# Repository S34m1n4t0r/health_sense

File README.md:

# Health Sense

Health Sense is a repository that houses the design files for a portable sensor module specifically designed to measure the light intensity in the spectrum of the human eye. This module is primarily developed for research purposes to accurately quantify the light exposure experienced by the human eye.

## Table of Contents
- [Introduction](#introduction)
- [Features](#features)
- [Revisions](#Revisions)
- [Sensors Used](#sensors-used)
- [Getting Started](#getting-started)
- [Usage](#usage)
- [Contributing](#contributing)
- [License](#license)

## Introduction

The human eye is highly sensitive to light, and prolonged exposure to certain intensities and spectrums can have various effects on our overall health and well-being. The Health Sense project aims to provide researchers with a reliable and portable tool for measuring light exposure and analyzing its impact on human subjects.

This repository contains the design files and relevant documentation for the Health Sense sensor module. By using this module, researchers can gather accurate data on light exposure, which can be further utilized for scientific studies, understanding circadian rhythms, evaluating the effects of light on sleep patterns, and other related research areas.

## Features

- **Portable Design**: The Health Sense sensor module is designed to be compact and portable, allowing researchers to easily carry and use it in different environments.
- **Light Intensity Measurement**: The module accurately measures the light intensity in the spectrum of the human eye, providing valuable data for research purposes.
- **Customizable Spectral Range**: Researchers can adjust the spectral range of measurement based on their specific requirements, enabling flexibility in studying different light sources.
- **Data Logging**: The module is equipped with data logging capabilities, allowing researchers to record and analyze light exposure data over extended periods of time.
- **User-Friendly Interface**: The sensor module includes a user-friendly interface, making it easy to operate and configure the device for different research settings.

## Revisions
### Prototyping
Breadboard setup created to verify the correct functionallity of all included sensors.

### Revision 1.0
Two prototypes are manufactured and assembled by hand as a final POC. The uC is loaded with the arduino-bootloader.

### Revision 1.1
Five prototypes are manufactured and assembled. Enclosure holes are milled with CNC.

### Known Issues
* Enable transistor for SIM800L not working
* SIM800L as solder-on pcb not optimal. 2/5 modules hat to be replaced.
* Charging current of 100mA could be increased
* Temperature Sensor of lipo not connected to charger IC

## Sensors Used

The Health Sense sensor module incorporates the following sensors:

- Ambient Light Sensor (BH1750): Measures light intensity in the visible spectrum.
- UV-B Sensor (GUVA-S12SD): Measures light intensity in the ultraviolet spectrum.
- Gyroscope Sensor (MPU-6050): Detects and measures orientation and rotation.
- RTC Clock (PCF8563TS): Provides accurate timekeeping functionality for scheduling and data timestamping.
- UMTS Module (SIM800L): Enables communication and data transmission via UMTS cellular network.

The integration of these sensors allows for comprehensive data collection and analysis related to light exposure in the context of research.

## Getting Started

To get started with the Health Sense sensor module, follow the steps below:

1. **Hardware Requirements**: Ensure you have the necessary components to assemble the sensor module. Refer to the [BOM](docs/BillOfMaterials_v1.1.csv) and [Schematic](HealthSenseSchematic_v1.1.pdf) for detailed information.

2. **Software Setup**: Install the Arduino IDE, the firmware hexfile can be generated using the arduino ide, choose the Nano Board. Flash the firmware via ISP connector J1.

3. **Calibration**: Before using the sensor module, it is important to calibrate it for accurate light intensity measurements.

4. **Usage**: Once the sensor module is assembled, calibrated, and ready, you can start using it to measure light exposure in your research. See the [Usage](#usage) section for more details.

## Usage

To utilize the Health Sense sensor module for measuring light exposure, follow these steps:

1. Connect the sensor module to a power source and ensure it is properly configured.

2. Position the module in the desired location to measure the light exposure of the human eye.

3. Initiate the measurement process by using the provided software interface or API. The module will start recording light intensity data in the specified spectral range.

4. Allow the module to collect data for the desired duration. The logged data can be stored internally or transmitted to an external device for analysis.

5. Analyze the collected data using appropriate data analysis tools to draw insights and conclusions regarding light exposure in your research.

Refer to the [User Guide](docs/user_guide.md) for detailed instructions on using the Health Sense sensor module effectively.

## Contributing

We welcome contributions from the community to enhance the Health Sense project. 

## License

The Health Sense project is licensed under the [GNU GENERAL PUBLIC LICENSE
](LICENSE). 

## Contact

For any inquiries or feedback regarding the Health Sense project, please contact our team. We appreciate your interest and support!

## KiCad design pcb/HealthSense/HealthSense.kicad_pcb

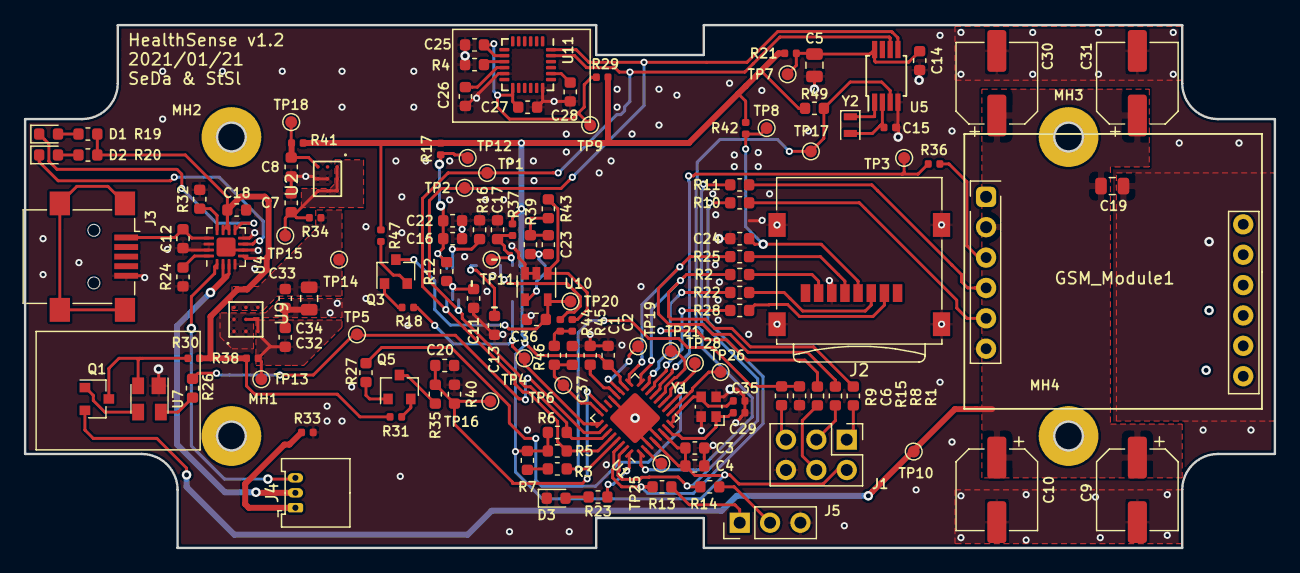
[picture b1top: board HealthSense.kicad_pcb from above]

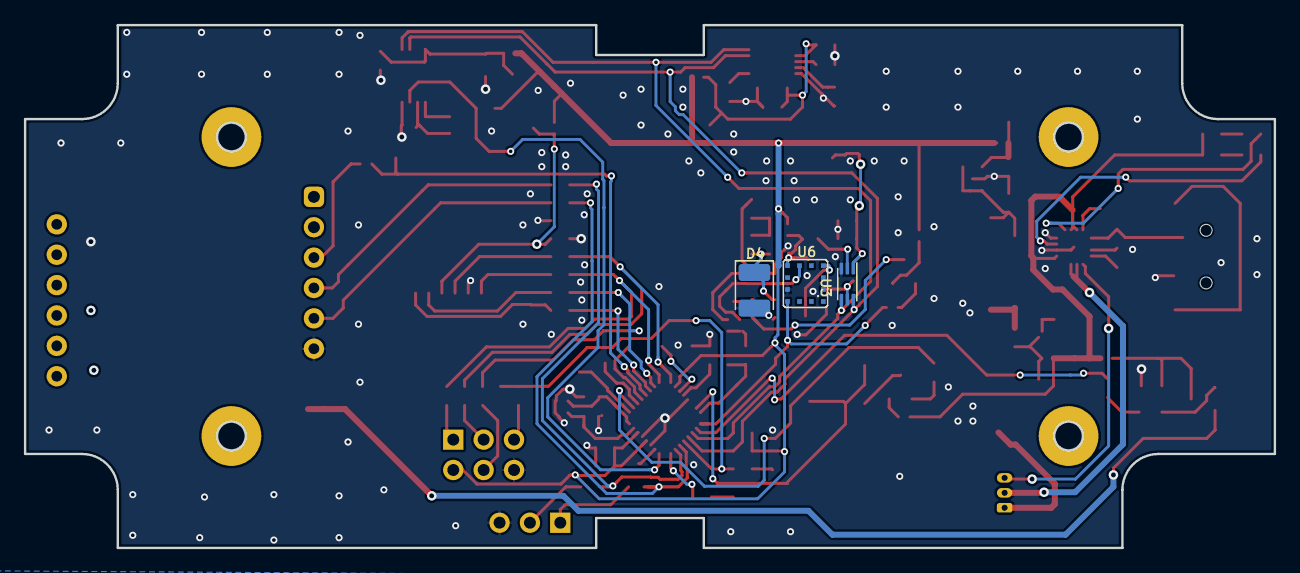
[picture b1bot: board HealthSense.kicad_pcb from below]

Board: 2 copper layers, 104.5 x 43.7 mm, 137 parts (3 on the bottom side), 85 nets.

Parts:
C1, C2, C3, C7, C8, C11, C14, C20, C22, C23, C24, C25, C26, C27, C32, C33, C36: 100n; C_0603_1608Metric
C4, C12, C16, C18: 10u; C_0603_1608Metric
C5, C19, C34: 22u; C_0805_2012Metric
C6, C13, C17: n.B.; C_0603_1608Metric
C9, C10: 865060245006; CP_Elec_6.3x5.8
C15, C29, C35: 22p; C_0402_1005Metric
C28, C37: 2n2; C_0603_1608Metric
C30, C31: n.B.; CP_Elec_6.3x5.8
D1: LEDG; D_0603_1608Metric
D2, D3: LEDR; D_0603_1608Metric
D4: GUVA-S12SD; D_1210_3225Metric_Pad1.42x2.65mm_HandSolder
GSM_Module1: n.B.; SIM800L
J1: ISP; PinHeader_2x03_P2.54mm_Vertical
J2: Micro_SD_Card; microSD_HC_Wuerth_693072010801
J3: USB_B_Mini; USB_Mini-B_Lumberg_2486_01_Horizontal
J4: Conn_01x03; Molex_PicoBlade_53048-0310_1x03_P1.25mm_Horizontal
J5: Conn_01x03; PinHeader_1x03_P2.54mm_Vertical
MH1, MH2, MH3, MH4: MountingHole; MountingHole_2.5mm_Pad
Q1: Q_NMOS_GSD; SOT-23
Q3, Q5: BC857; SOT-23
R1, R8, R9, R15: 100R; R_0603_1608Metric
R2, R3, R4, R5, R6, R7, R10, R11, R12, R13, R14, R16, R19, R20, R22, R23, R25, R26, R28, R46: 1K; R_0603_1608Metric
R17, R21, R29, R30, R31, R33, R34, R38, R41, R42, R45, R47: 0R; R_0402_1005Metric
R18: 47K; R_0402_1005Metric
R24: 6K; R_0603_1608Metric
R27, R35, R49: 100K; R_0603_1608Metric
R32, R43: 3K3; R_0603_1608Metric
R36, R37, R44: n.B.; R_0402_1005Metric
R39: 7M15; R_0603_1608Metric
R40: 220k; R_0603_1608Metric
TP1, TP2, TP3, TP4, TP5, TP6, TP7, TP8, TP9, TP10, TP11, TP12, TP13, TP14, TP15, TP16, TP17, TP18, TP19, TP20, TP21, TP25, TP26, TP28: TestPoint; TestPoint_Pad_D1.0mm
U1: ATmega328P-MU; QFN-32-1EP_5x5mm_P0.5mm_EP3.1x3.1mm
U2: TPS82740; uSIP-9pin-2.3x2.9mm
U3: BH1750; WSOF6I
U4: BQ24072RGT; VQFN-16-1EP_3x3mm_P0.5mm_EP1.6x1.6mm
U5: PCF8563TS; MSOP-8_3x3mm_P0.65mm
U6: n.B.; ML8511
U7: MIC5018; SOT-143
U9: TPS81256; uSIP-9pin-2.57x2.9mm
U10: MCP6001-OT; SOT-23-5
U11: MPU-6050; InvenSense_QFN-24_4x4mm_P0.5mm
Y1: Crystal; Crystal_SMD_Abracon_ABM10-4Pin_2.5x2.0mm
Y2: 32.678k; Crystal_SMD_2012-2Pin_2.0x1.2mm

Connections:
+3V3: C2.1, C3.1, C4.1, J1.2, R5.2, R6.2, R7.2, R17.2, R21.1, R29.2, R37.1, R41.2, R42.1, R47.1, R49.2, U1.4, U1.6, U1.18
+5V: C33.1, C34.1, R34.1, TP14.1, U9.A3, U9.B3, U9.C3
/A_VBAT: C20.1, R35.1, R40.2, TP16.1, U1.23
/EN_A_VBAT: R27.1, U1.10
/EN_SIM: R26.1, TP5.1, U1.26
/Light/UV1_OUT: R44.2, U6.8
/Light/UV2_OUT: R43.1, R45.2, U10.1
/MISO: R1.1, R2.2, U1.16
/MOSI: R15.2, R22.2, U1.15
/RESET: C6.1, R3.1, R9.1, U1.29
/RESET_SIM: R36.1, TP3.1, U1.13
/RTC_INT: R49.1, TP17.1, U1.1, U5.3
/RX: R10.1, R13.2, U1.30
/RX_PROG: J5.1, R13.1
/SCK: R8.1, R25.2, U1.17
/SCL: R5.1, TP1.1, U1.28, U3.6, U5.6, U11.23
/SD/S_CS: J2.2, R28.1
/SD/S_DI: J2.3, R22.1
/SD/S_DO: J2.7, R2.1
/SD/S_SCK: J2.5, R25.1
/SDA: R6.1, TP2.1, U1.27, U3.4, U5.5, U11.24
/SD_CS: R28.2, U1.14
/TX: R11.1, R14.2, U1.31
/TX_PROG: J5.2, R14.1
/USB/BAT+: J4.2, U4.2, U4.3
/USB/BAT-: J4.1, R33.1
/USB/TS: J4.3, U4.1
/UV_EN: R18.2, TP4.1, U1.25, U6.4
/UV_OUT: C37.1, R46.2, TP6.1, U1.24
GND: C1.2, C2.2, C3.2, C4.2, C5.2, C6.2, C7.2, C8.2, C9.2, C10.2, C11.2, C12.2, C13.2, C14.2, C15.1, C16.2, C17.2, C18.2, C19.2, C20.2, C22.2, C24.2, C25.2, C26.2, C27.2, C28.2, C29.1, C30.2, C31.2, C32.2, C33.2, C34.2, C35.1, C36.2, C37.2, D3.1, D4.2, GSM_Module1.6, J1.6, J2.6, J2.9, J3.5, J5.3, R4.2, R16.1, R24.1, R32.1, R33.2, R40.1, U1.3, U1.5, U1.21, U1.33, U2.B2, U2.C2, U3.3, U4.4, U4.6, U4.8, U4.14, U4.15, U4.17, U5.4, U6.5, U7.1, U9.A1, U9.A2, U9.B1, U10.2, U10.3, U11.11, U11.18, Y1.2, Y1.4
unnamed: C1.1, U1.20
unnamed: C7.1, R34.2, TP15.1, U2.A1, U2.A2, U2.A3, U2.B3, U2.C3
unnamed: C8.1, R41.1, TP18.1, U2.C1
unnamed: C9.1, C10.1, C19.1, C30.1, C31.1, GSM_Module1.2, Q1.2, TP10.1
unnamed: C11.1, R12.1, U3.5
unnamed: C12.1, J3.1, U4.13
unnamed: C13.1, U6.10
unnamed: C5.1, C14.1, R21.2, TP7.1, U5.8
unnamed: C15.2, U5.2, Y2.2
unnamed: C16.1, C22.1, R12.2, R17.1, TP12.1, U3.1
unnamed: C17.1, R37.2, TP11.1, U6.7
unnamed: C23.1, R39.1, R43.2
unnamed: C23.2, D4.1, R39.2, U10.4
unnamed: C24.1, J2.4, R42.2, TP8.1
unnamed: C25.1, C27.1, R29.1, TP9.1, U11.8, U11.13
unnamed: C26.1, U11.10
unnamed: C28.1, U11.20
unnamed: C29.2, U1.7, Y1.1
unnamed: C32.1, R38.2, TP13.1, U9.B2, U9.C1, U9.C2
unnamed: C35.2, U1.8, Y1.3
unnamed: C36.1, Q3.3, TP20.1, U10.5
unnamed: D1.1, U4.9
unnamed: D1.2, R19.1
unnamed: D2.1, U4.7
unnamed: D2.2, R20.1
unnamed: D3.2, R23.1
unnamed: GSM_Module1.3, R36.2
unnamed: GSM_Module1.4, R11.2
unnamed: GSM_Module1.5, R10.2
unnamed: J1.1, R1.2
unnamed: J1.3, R8.2
unnamed: J1.4, R15.1
unnamed: J1.5, R9.2
unnamed: Q1.1, U7.3
unnamed: Q1.3, R30.2, U7.2
unnamed: Q3.1, R18.1
unnamed: Q3.2, R47.2
unnamed: Q5.1, R27.2
unnamed: Q5.2, R31.2
unnamed: Q5.3, R35.2
unnamed: R3.2, R7.1
unnamed: R4.1, U11.9
unnamed: R16.2, U3.2
unnamed: R23.2, U1.32
unnamed: R24.2, U4.16
unnamed: R26.2, U7.4
unnamed: R32.2, U4.12
unnamed: R44.1, R45.1, R46.1
unnamed: TP19.1, U1.19
unnamed: TP21.1, U1.12
unnamed: TP25.1, U1.2
unnamed: TP26.1, U1.9
unnamed: TP28.1, U1.11
unnamed: U5.1, Y2.1
VCOM: C18.1, R19.2, R20.2, R30.1, R31.1, R38.1, U4.5, U4.10, U4.11

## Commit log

2023-07-16 Updated Documentation
